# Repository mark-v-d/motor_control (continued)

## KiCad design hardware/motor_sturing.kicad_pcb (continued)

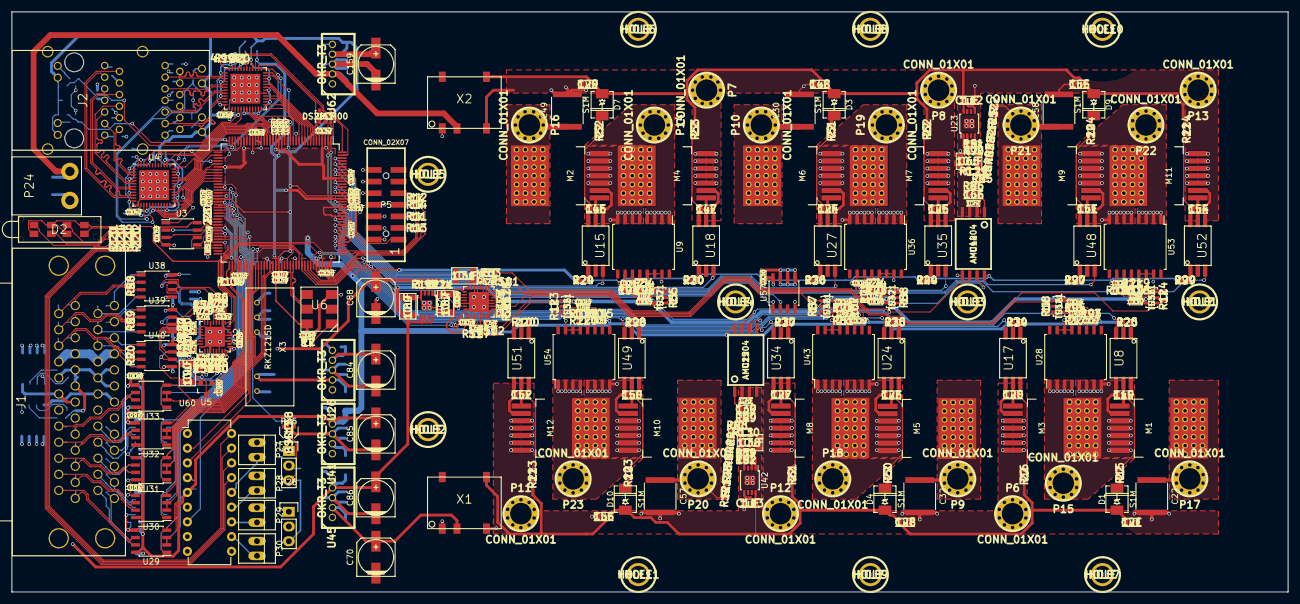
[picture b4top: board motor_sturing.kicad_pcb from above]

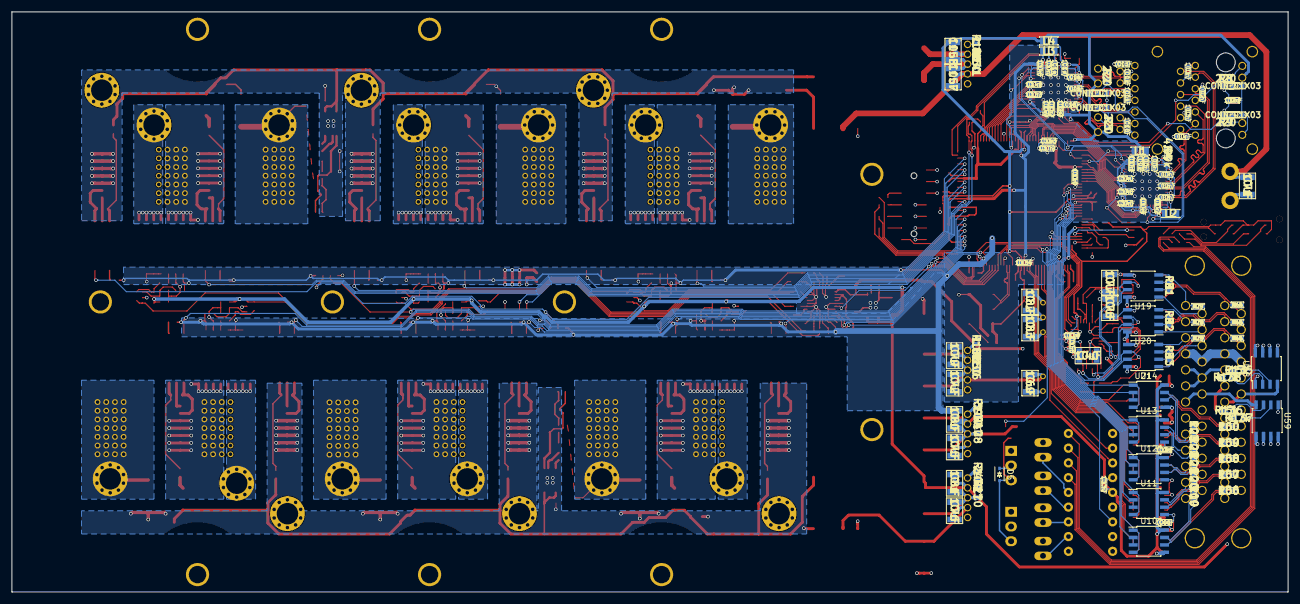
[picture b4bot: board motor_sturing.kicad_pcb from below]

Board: 4 copper layers, 220.0 x 100.0 mm, 433 parts (112 on the bottom side), 355 nets.

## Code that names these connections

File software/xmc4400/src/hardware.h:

#ifndef HARDWARE_H
#define HARDWARE_H

#include <chrono>
#include <atomic>
#include <stdint.h>
#include "gpio.h"
#include "ccu8.h"
#include "hrpwm0.h"

constexpr float trigger_HZ=4500.0;

extern std::atomic<uint32_t> sleep_counter;

template <class T>
inline void sleep(T time)
{
    using tick_t=std::chrono::duration<uint32_t,std::ratio<1,int(trigger_HZ)>>;
    auto ticks=std::chrono::duration_cast<tick_t>(time);
    sleep_counter;
    while(sleep_counter<ticks.count())
	;
}

void set_timestamp();
uint32_t get_timestamp();

#include "gpio.h"

static gpio::output<3,6> LED0; // TRACED3
static gpio::output<4,0> LED1; // TRACED2
static gpio::output<4,1> LED2; // TRACED1
static gpio::output<1,15> LED3; // TRACED0
static gpio::output<2,14> TRACECLK;

static gpio::pin<15,8> CLK_RMII;
static gpio::pin<5,2> CRS_DV;
static gpio::pin<5,0> RXD0;
static gpio::pin<5,1> RXD1;
static gpio::pin<0,11> RXER;
static gpio::pin<2,7> MDC;
static gpio::pin<2,0> MDIO;
static gpio::pin<2,8> TXD0;
static gpio::pin<2,9> TXD1;
static gpio::pin<1,12> TX_EN;
static gpio::output<2,10> ETH_RESET;
static gpio::output<0,9> SUPPLY_VOLTAGE;
static hrpwm0::out<0,6> FAN;
static gpio::pin<2,1> TRACESWO;


static hrpwm0::out<0,5> HBL0_HR;
static hrpwm0::out<0,2> HBH0_HR;
static hrpwm0::out<0,8> HBL1_HR;
static hrpwm0::out<0,7> HBH1_HR;
static hrpwm0::out<0,3> HBL2_HR;
static hrpwm0::out<0,4> HBH2_HR;

//static gpio::output<0,10> HBEN;

static gpio::output<1,2> ENC_5V;
static gpio::output<1,3> ENC_12V;
static gpio::output<1,10> ENC_DIR;
static gpio::pin<1,5> ENC_TXD;
static gpio::pin<1,4> ENC_RXD;
//static gpio::pin<0,0> ENC_RXD2;
static gpio::output<1,1> ENC_CLK;

static gpio::pin<14,7> ENC_SIN;
static gpio::pin<14,12> ENC_SIN_A;
static gpio::pin<14,6> ENC_COS;

static gpio::output<5,7> ENC_DDIR; // sub-d9
static gpio::output<2,6> ENC_CDIR;
static gpio::pin<2,5> ENC_A;
static gpio::pin<2,4> ENC_B;
static gpio::pin<2,3> ENC_Z;

static gpio::pin<0,0> COPRO_RXD;
static gpio::pin<0,1> COPRO_TXD;
static gpio::output<0,10> COPRO_POWER;

static gpio::output<1,13> IO0;
static gpio::output<1,0> IO1;
static gpio::output<1,9> IO2;
static gpio::output<1,8> IO3;
static gpio::output<1,7> IO4;
static gpio::output<1,6> IO5;
static gpio::output<3,5> IO6;
static gpio::output<3,4> IO7;

static gpio::output<3,2> RELAY0;
static gpio::output<3,1> RELAY1;

static gpio::pin<14,0> AN_IN0;
static gpio::pin<14,1> AN_IN1;
static gpio::pin<14,2> AN_IN2;
static gpio::pin<14,3> AN_IN3;
static gpio::pin<14,4> AN_IN4;
static gpio::pin<14,5> AN_IN5;
static gpio::pin<14,13> TPOWER;

using namespace std::chrono_literals;

constexpr ccu8::resolution_t pwm_time=1.0s/18000;

/*
    Allocated units:
    CCU80 -> PWM
    CCU40 -> POSIF0
    CCU41 -> POSIF1
*/

#endif

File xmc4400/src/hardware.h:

#ifndef HARDWARE_H
#define HARDWARE_H

#include <chrono>
#include <atomic>
#include <stdint.h>
#include "gpio.h"
#include "pwm_3phase.h"

constexpr float trigger_HZ=4500.0;

extern std::atomic<uint32_t> sleep_counter;

template <class T>
inline void sleep(T time)
{
    using tick_t=std::chrono::duration<uint32_t,std::ratio<1,int(trigger_HZ)>>;
    auto ticks=std::chrono::duration_cast<tick_t>(time);
    sleep_counter=0;
    while(sleep_counter<ticks.count())
	;
}

#include "gpio.h"

static gpio::output<3,6> LED0=1;
static gpio::output<4,0> LED1=1;
static gpio::output<4,1> LED2=1;
static gpio::output<1,15> LED3=1;
static gpio::output<2,14> LED4=1;
static gpio::pin<15,8> CLK_RMII;
static gpio::pin<5,2> CRS_DV;
static gpio::pin<5,0> RXD0;
static gpio::pin<5,1> RXD1;
static gpio::pin<0,11> RXER;
static gpio::ETH0_MDC<2,7> MDC;
static gpio::ETH0_MDO<2,0> MDIO;
static gpio::ETH0_TXD0<2,8> TXD0;
static gpio::ETH0_TXD1<2,9> TXD1;
static gpio::ETH0_TX_EN<1,12> TX_EN;
static gpio::output<2,10> ETH_RESET=1;

static gpio::CCU80_OUT20<0,3> HB1;
static gpio::CCU80_OUT00<0,5> HB0;
static gpio::CCU80_OUT30<0,6> HB2;
extern pwm_3phase <decltype(HB0),decltype(HB1),decltype(HB2)>pwm;

//static gpio::output<0,10> HBEN=1;

static gpio::output<1,2> ENC_5V=0;
static gpio::output<1,3> ENC_12V=0;
static gpio::output<1,10> ENC_DIR=0;
static gpio::U0C0_DOUT0<1,5> ENC_TXD; // FIXME, HWCTRL should only be used fo SSI
static gpio::pin<1,4> ENC_RXD;
//static gpio::pin<0,0> ENC_RXD2;

static gpio::pin<14,7> ENC_SIN;
static gpio::pin<14,6> ENC_COS;

static gpio::pin<2,5> ENC_A;
static gpio::pin<2,4> ENC_B;
static gpio::pin<2,3> ENC_Z;


/*
    Allocated units:
    CCU80 -> PWM
    CCU40 -> POSIF0
    CCU41 -> POSIF1 (FIXME, do this)
    ERU1,ETLx,OGU2 -> x=pwm.spare_slice(), latch posif counter
*/

#endif

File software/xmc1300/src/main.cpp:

#include "uart.h"
#include "vadc.h"
#include "ccu4.h"
#include "crc.h"
#include <array>

using namespace std::chrono_literals;

gpio::output<0,0> DAC;
gpio::pin<0,14> RXD;
gpio::pin<0,15> TXD;
gpio::pin<2,0> I0_P;
gpio::pin<2,11> I1_P;
gpio::pin<2,8> I2_P;
gpio::pin<2,10> V;
gpio::pin<0,9> RXD_TIMER;

gpio::output<0,6> DEBUG;

uart::full_duplex serial(TXD,RXD);
ccu4::edge_capture<0,3> serial_capture;

extern "C" void USIC0_0_IRQHandler(void)
{
    static_assert(serial.UNIT==0, "Wrong uart");
    DEBUG=1;

    adc::queue<0>(I0_P,	adc::EXTERNAL_TRIGGER);
    adc::queue<0>(V, adc::ENSI);
    adc::queue<1>(I1_P,	adc::EXTERNAL_TRIGGER);
    adc::queue<1>(I2_P, 0);

    serial->PSCR=USIC_CH_PSCR_CRIF_Msk;
}

extern "C" void VADC0_G0_0_IRQHandler(void)
{
    DEBUG=0;
    std::array<uint16_t,5> data;
    serial.tx_fifo(data[0]=adc::vadc.G[0].RES[0]);
    serial.tx_fifo(data[1]=adc::vadc.G[1].RES[0]);
    serial.tx_fifo(data[2]=adc::vadc.G[0].RES[1]);
    serial.tx_fifo(data[3]=adc::vadc.G[1].RES[1]);
    serial.tx_fifo(data[4]=adc::vadc.G[0].SEFLAG | (adc::vadc.G[1].SEFLAG<<8));
    serial.tx_fifo(crc::ccitt_16(data).get());
    adc::vadc.G[0].SEFCLR=VADC_G_SEFCLR_SEV0_Msk;
    adc::vadc.G[1].SEFCLR=VADC_G_SEFCLR_SEV0_Msk;
}

int main(int argc, char **argv)
{
    DAC.set(XMC_GPIO_MODE_OUTPUT_PUSH_PULL);
    DEBUG=1;DEBUG.set(XMC_GPIO_MODE_OUTPUT_PUSH_PULL);

    ////////////////////////////////////////////////////////////////////////////
    // UART
    ////////////////////////////////////////////////////////////////////////////
    serial.init(uart::Baudrate(4e6));
    uart::fifo_configure<16,8>(serial);
    serial.enable_rx_interrupt<0>();
    NVIC_EnableIRQ(serial.irq<0>());

    ////////////////////////////////////////////////////////////////////////////
    // Timer used to trigger the ADC
    ////////////////////////////////////////////////////////////////////////////
    ccu4::init<0>(
	XMC_CCU4_CLOCK_SCU,
	XMC_CCU4_SLICE_MCMS_ACTION_TRANSFER_PR_CR
    );

    serial_capture.init();
    //serial_capture.period(1s/20000.0f);
    serial_capture.set_event<1>(RXD_TIMER,ccu4::EDGE_FALLING);
    serial_capture.service_request_event<1>(2); // trigger ADC
    //serial_capture.enable_capture<0>(1);

    ccu4::start(serial_capture);
    ccu4::shadow_transfer(serial_capture);

    ////////////////////////////////////////////////////////////////////////////
    // ADC
    ////////////////////////////////////////////////////////////////////////////
    adc::init();
    adc::global_class<0>(XMC_VADC_CONVMODE_12BIT,8);
    adc::channel_control<0>(I0_P, XMC_VADC_CHANNEL_CONV_GLOBAL_CLASS0, 0);
    adc::channel_control<0>(V,	  XMC_VADC_CHANNEL_CONV_GLOBAL_CLASS0, 1);
    adc::channel_control<1>(I1_P, XMC_VADC_CHANNEL_CONV_GLOBAL_CLASS0, 0);
    adc::channel_control<1>(I2_P, XMC_VADC_CHANNEL_CONV_GLOBAL_CLASS0, 1);
    adc::queue_config<0>( XMC_VADC_GATEMODE_IGNORE, 0,
	XMC_VADC_REQ_TR_CCU40_SR2, XMC_VADC_TRIGGER_EDGE_RISING
    );
    adc::queue_config<1>( XMC_VADC_GATEMODE_IGNORE, 0,
	XMC_VADC_REQ_TR_CCU40_SR2, XMC_VADC_TRIGGER_EDGE_RISING
    );

    for(int i: {0,1}) {
	adc::vadc.G[i].ARBPR=
	    bitfield<VADC_G_ARBPR_PRIO0_Msk>(3) |
	    VADC_G_ARBPR_CSM0_Msk |
	    VADC_G_ARBPR_ASEN0_Msk;
	adc::vadc.G[i].ARBCFG=
	    bitfield<VADC_G_ARBCFG_ANONC_Msk>(3) |
	    bitfield<VADC_G_ARBCFG_ANONS_Msk>(3);
    }

    NVIC_EnableIRQ(VADC0_G0_0_IRQn);

    for(;;) {
    }
    return 0;
}

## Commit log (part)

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2016-02-22 Before moving to SiC fets.
2016-03-03 Backup, clearing bottom of power section.
2016-03-07 Progress.
2016-07-10 First small drive hardware.
2016-07-11 Before splitting.
2016-07-15 Adding order codes
2016-07-15 Remove unused files.
2016-07-21 Allow register dump.
2016-07-21 Concept IO initialisation.
2016-07-22 Allow parsing of classes.
2016-07-22 Encoder now started by DMA.
2016-07-24 Working space vector mapping.
2016-07-25 Oops wrong sign for phase->orth current.
2016-08-04 Adding XMC4400 processor test.
2016-08-04 Adding Makefile
2016-08-04 Adding main.cpp
2016-08-04 Adding XMC4500.h
2016-08-04 Adding more CMSIS files
2016-08-04 Even more CMSIS files
2016-08-06 Adding FreeRTOS.
2016-08-16 Pauze backup
2016-08-16 Moved enable opto.
2016-08-20 Fresh start with the software.
2016-08-20 Proof of concept to check pin usage.
2016-08-21 Ethernet MAC started.
2016-08-21 Ping works.
2016-08-22 Cleanup SysTick.
2016-08-23 Add missing phy source.
2016-08-23 Add icmp.h
2016-09-17 Header conversion in C++
2016-09-18 Should work but doesn't enter main
2016-09-18 OK, we can now handle exceptions.
2016-09-20 Initial test on XMC4400, LED0/mdc/mdio works.
2016-09-25 Reduce binary size by adding proper std::terminate
2016-09-25 Test throwing.
2016-09-28 Can receive packets on the xmc4400, ping does not work yet.
2016-09-28 Ping works on xmc4400.
2016-09-30 PWM (low resolution) works.
2016-09-30 Functional PWM, including subsampling interrupt.
2016-10-01 Software triggered encoder read works.
2016-10-02 Encoder responds.
2016-10-18 Working logger on board.
2016-10-18 Working logger on PC.
2016-10-25 Stop transmitting on unreachable UDP port.
2016-11-01 Trigger UART with timer.
2016-11-27 Can start controlling with octave again.
2016-11-27 All bridges word. Cannot re-program from octave.
2016-12-13 Mitsubishi encoder detection works.
2016-12-13 Cleanup encoder interrupt handling.
2016-12-13 Cleanup main.cpp moved encoder functions to encoder.cpp
2016-12-18 Cleanup encoder code.
2016-12-20 Hiperface digital part works.
2016-12-21 Cleanup sleeping.
2016-12-24 Hiperface without interpolation works.
2016-12-24 DSD works for the AMC1204.
2016-12-25 Removed xmc_dsd.o
2017-01-08 Assign unique MAC address to each board.
2017-01-08 More fields in the logger.
2017-01-08 Make sure the ping echo has the actual MAC address.
2017-01-08 Update MAC addresses.
2017-01-14 Adding timestamp. Fixed port numbers.
2017-01-15 Cleanup input conversion functions. Allow ipv4 address setting with ping.
2017-01-15 Starting synchroniser.
2017-01-18 udp_sync locks to the PC in 3 seconds.
2017-01-20 Very crude PWM synchronisation
2017-01-22 Improved PWM synchronisation
2017-01-23 Cleanup of pwm_3phase, now allow multiple instances.
2017-01-30 Do not respond on a sync broadcast.
2017-01-30 Update gitignores.
2017-01-30 Real-time logger added. HAL started.
2017-01-30 Working sync from linuxcnc
2017-02-03 Hiperface interpolation (needs hardware patches)
2017-02-03 Convert etherdrive to C++
2017-02-04 Fixed receiver overflow for the PQ23 motor.
2017-02-05 MFS13 fixes
2017-02-05 Working lathe config.
2017-02-05 Repair Hiperface
2017-02-05 Add license.
2017-02-05 Prevent Ethernet MMC interrupts.
2017-02-06 Fix mitsubishi PQ23 encoder zero wrap.
2017-02-11 Adding comments to the sync method.
2017-03-01 Use make_unique to initialise encoder.
2017-03-01 New small_drive, untested, unverified.
2017-04-02 Adding more advanced speed observer model.
2017-04-02 Configuring the lathe, work in progress.
2017-04-02 Properly functioning velocity estimator.
2017-04-15 Fixing current ripple
2017-04-17 Use 5V for opamp supply.
2017-04-30 Velocity estimator, HB04, G71.
2017-04-30 Remove compiled python.
2017-05-01 Glass scale first test
2017-05-06 Made posif 32-bit in timer. Encoder fails when the drive is not yet synchronised.
2017-05-06 Using capture for position and index for POSIF. Fixed occasional problem with half_duplex transmission.
2017-05-06 Interface for glass-scale
2017-05-07 Initial indexing tests.
2017-05-10 Adding homing.
2017-07-19 Use printerport instead of USB relays.
2017-11-19 Adding script to used to tune the PQ23 motor on the z-axis.
2019-01-02 Adding power_stage for high voltage drive.
2019-01-02 Adding sym-lib-table for power stage
2019-02-17 Control stage, initial version.
2021-01-03 Starting software on hv_drive
2021-01-03 Make decode and parse static linked
2021-01-10 Initial xmc1300 code.
2021-01-10 Rename iopin to gpio::pin and gpio::output
2021-01-18 xmc1300 can toggle pin.
2021-01-19 Only rebuild when needed
2021-01-23 Restructure with XMCLib as submodule
2021-01-23 Removing old XMCLib.
2021-01-23 Add bootstrap loader.
2021-01-24 Uarrt code works.
2021-01-24 Adding interrupt names to VCD file.
2021-01-31 Adding scripts to use the parallel trace port. Only 4-bit interface tested.
2021-02-01 Improved clock recovery for traceport. Made VCD time always integers.
2021-02-05 Use anonymous function in nelder_mead_min.
2021-02-06 Using fft to find the carrier frequency.
2021-12-30 Assembling hv_power.
2022-01-10 Initial working version of new ccu8 code.
2022-01-10 Removing references to old CCU8 code.
2022-01-11 Cleanup, interface for ccu8 and hrpwm0 are (except for init) identical.
2022-01-11 Remoce normal resolution timer from main.cpp
2022-01-11 Adding float field to itm.PORT
2022-01-12 Proper high resolution.
2022-01-12 HRPWM0 pins are unique, so only require port and pin to identify.
2022-01-15 Backup ccu8.h
2022-01-16 Reduced uart interface, turned CCU80 on on the XMC1300
2022-01-23 Adding missing file
2022-01-23 Fix ITM_Type locally
2022-01-23 Allow crc-ing blocks.
2022-01-30 Using falling edge of start-bit on the XMC1300 to trigger the ADC. Routed using P0.9 and CCU40_CC3.
2022-02-01 Start transmitting after ADC is finished.
2022-02-09 MFS13 encoder using new uart driver.
2022-02-14 Space vector mapping and current measurement work.
2022-02-14 Motor runs, encoder checksum does not work.
2022-02-15 Current control works, changed shadow transfer moment.
2022-02-15 Move common fields to encoder_t. Set CCU8 safe debug stop.
2022-02-19 Ethernet starts (make sure to enable digital input)
2022-02-19 Cleanup space_vector_mapping
2022-02-21 Ethernet ping works.
2023-01-29 Adding raw packet/realtime send test. Latency too large.
2023-01-30 Put pulses on the printerport. Latency was fixed with: ethtool -C eth2 rx-usecs 0
2023-02-05 Start working on PWM synchronisation.
2023-02-07 Ethernet sync WIP.
2023-02-12 Adding trajectory generator for motion tests.
2023-02-13 Adding raw_socket class.
2023-02-13 Adding checksum computation.
2023-02-13 Change various C arrays to std::array.
2023-02-19 Move everything to the same drive_packet.h. Add age function to udp_struct.
2023-02-19 Start motion test.
2023-02-21 Add ethernet_map.h
2023-02-23 PLL lock detection works.
2023-03-05 motion_test can set current.
2023-03-12 Adding posif interface (not tested)
2023-03-19 Enable MFS13 encoder.
2023-03-19 Reduce interrupts for Mitsubishi PQ motors as well.
2023-03-19 Cleanup enable receive buffer interrupt.
2023-06-11 Disable PWM on ethernet loss.
2023-08-02 Adding AMT21 encoder (untested)
2023-10-17 Extend AMT21 encoder to 21-bits. motion-test in two directions. Keep old position if encoder fails
2023-10-19 Ordered new boards.
2023-11-08 Fix orientation/polarity of current/encoder/voltage. Modified for board v2 (COPRO_POWER)
2023-11-10 Set the run bit in the timer for the POSIF.
2023-11-11 Allow speed limit when testing.
2023-11-19 Add 2nd order state space controller. Use all three current measurements to reduce noise.
2023-11-24 Scripts for higher order current control loops.
2023-11-24 Before testing oversampling.
2023-11-25 Adding motion control loop test.
2023-11-25 Adding file to save position control parameters.
2023-11-26 These values seem pretty optimal for the Z-axis.
2023-12-03 Update encoder->ethernet timing. Improved gains. Removed position ripple by reducing misalignment of ball-screw.
2023-12-04 Allow simulation of the controller.
2023-12-06 Adding initial configuration packet.
2023-12-08 Changed motion_test2 to current setpoints and cleaned up the interface.
2023-12-10 Adding improved motion control loop test.
2023-12-10 Detect std::format
2023-12-13 Adding initial hal files for linuxcnc
2023-12-14 First noise from the drive.
2023-12-17 Both Z and X working. Need to re-tune. Add some kind of sub-resolution for position2
2023-12-18 Works again.
2023-12-21 Adding cpuinfo.m
2023-12-21 Trying to find out why we mis packets.
2023-12-22 Oops.
2023-12-22 Retune X after replacing the belt with a narrowwer version and loosen the bearings.
    TODO: Fix syncer lock detection.
2023-12-26 Comments for next version added.
2023-12-27 Start spindle drive.
2023-12-29 Try configuring the drives.
2023-12-29 Adding pendant.
2024-01-02 Initial test of voltage/speed control works.
2024-01-02 Decelerate at I=0, accelerate limited by either dV/dt or maximum current.
2024-01-03 Drives use DRIVE_ENABLE and data is updated before machine is turned on.
2024-01-04 Spindle works, overcurrent at high speeds.
2024-01-07 First actual turning done. Before starting threading.
2024-01-08 Oops, forgot the speed_controller.
2024-01-08 Must include <vector>
2024-01-08 Adding postgui hal file
2024-01-13 Adjust gains for 1um scale on X
2024-01-13 Lathe works with new linear encoder.
2024-01-13 Update flyback resistors, we're below 700V.
2024-01-13 Don't let NaN get into the integrator.
2024-01-15 Fixed indexing for Sino scales.
2024-01-22 Adding spindle load to gmoccapy.
2024-01-27 Occasionally the z-axis fails. Retry programming the copro.
2024-01-28 Constant surface speed kind of works.
2024-02-10 Retry if xmc1300 is not starting up properly.
2024-03-17 Adding temperature monitoring.
2024-07-03 Adding custom knob/button interface. Increase spindle acceleration.
2024-07-05 Comments for next hardware version.
2024-07-06 Updated readme.
2024-07-21 Adding drive temperature to simulation.
2024-07-21 Addint this tooltable as well
2024-07-21 Adding tool table, because it seems to break occasionally.
2024-07-21 Make speed_controller more robust. The CUI encoder is still repeating values.
2024-07-22 Adding subsampling to AMT21 encoder.
2024-07-23 Subsampling works for the AMT21.
2024-07-24 Minor cleanup of encoder interface.
2024-07-28 Get e-stop status from motor drives.
2024-07-28 This seems to fix the issue with the glass_scale not wanting to start decrementing until after an increment. The polarity of input A if flipped, and later flipped back. This way the encoder is counti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
2024-09-01 T12/14/16 new offsets.
2024-09-01 Updated tool settings.
2024-09-01 Backup before new front panel
2024-09-01 Updated encoder statistics. Adding drive status page en manual mode.
2024-09-09 Add PWM to the FAN output (wrong pin)
2024-09-09 Fan PWM on correct pin.
2024-09-09 Reduced the amount of code in hrpwm.h
2024-10-27 Change timing of measurements.
    Add incremental pulse encoder.
2024-11-04 Add missing h_bridge.sch
2025-08-31 First responses from the encoder.
2025-09-17 lathe.ini for simulation mode.
2025-09-17 Add missing file
2025-09-21 Add missing header file.
2025-09-28 Fanuc CRC works.
2025-10-03 Switch frame length ASAP, to make the the CRC is captured correctly. Removed debugging copy of Fanuc encoder message.
2025-10-04 Adding scripts to tune the current control loop.
2025-10-04 Put logging data into a structure.
2025-10-05 Adding dwell to mp.m
2025-10-05 Try to find and fix the occasional position error.
2025-10-06 Cleanup CRC code.
2025-10-06 Update the documentation of the Fanuc encoder.
2025-10-15 Adding type3 compensation instead of PID. This should reduce noise.
2025-10-17 X tuned using a type-3 compensation.
2025-10-18 Adding index for first encoder.
2025-10-22 Working, before homing.
2025-10-26 Moving to alpha2
2025-10-27 absolute_index seems to work from a cold and a warm start.
    Restarting the drives does not yet work.
2025-10-27 This also works at high speed while passing the index. Added z-axis.
2025-10-28 Cleanup of absolute_index.
